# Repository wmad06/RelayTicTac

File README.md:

# RelayTicTac
Relay logic Tic Tac Toe computer
bitfoot is coming!
POTATO!
I like to eat
LEMON!

potato + lemon = sour potato
sour + sweet = 0
sour potato + candy = potato
egg salad
This is a good use of the read me file

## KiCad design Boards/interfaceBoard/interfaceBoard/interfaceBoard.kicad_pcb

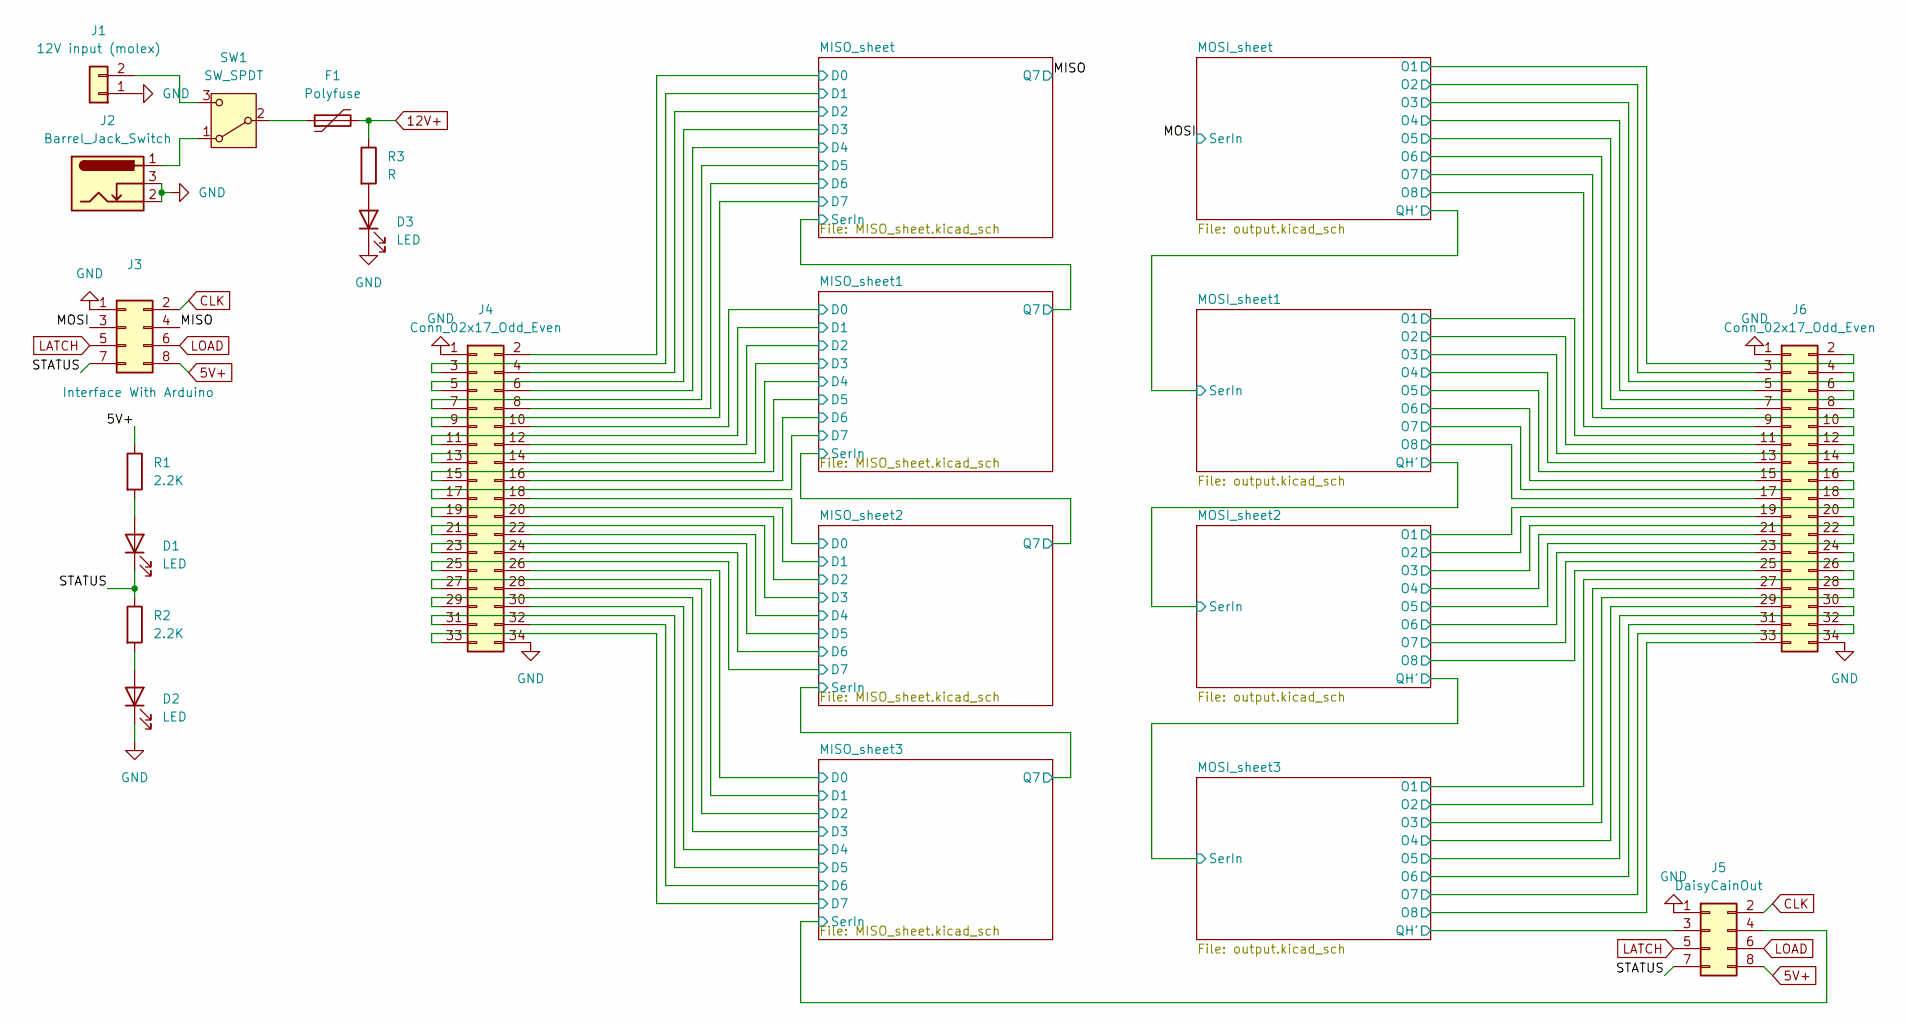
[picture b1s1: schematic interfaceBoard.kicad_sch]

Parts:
D1, D2, D3: LED; LED_D3.0mm
F1: Polyfuse; Fuse_Bourns_MF-RHT100
J1: 12V input (molex); CONN_SD-172648-0000_02_MOL
J2: Barrel_Jack_Switch; BarrelJack_Horizontal
J3: Interface With Arduino; PinHeader_2x04_P2.54mm_Vertical
J4, J6: Conn_02x17_Odd_Even; PinHeader_2x17_P2.54mm_Vertical
J5: DaisyCainOut; PinHeader_2x04_P2.54mm_Vertical
R1, R2: 2.2K; R_Axial_DIN0207_L6.3mm_D2.5mm_P10.16mm_Horizontal
R3: R; R_Axial_DIN0207_L6.3mm_D2.5mm_P10.16mm_Horizontal
SW1: SW_SPDT; SW_SPDT_SS-12D10L5

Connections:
5V+: J3.8, J5.8, R1.1; also elsewhere on the board
12V+: F1.2, R3.1; also elsewhere on the board
/MISO: J3.4; also elsewhere on the board
/MISO_sheet1/D0: J4.10; also elsewhere on the board
/MISO_sheet1/D1: J4.11; also elsewhere on the board
/MISO_sheet1/D2: J4.12; also elsewhere on the board
/MISO_sheet1/D3: J4.13; also elsewhere on the board
/MISO_sheet1/D4: J4.14; also elsewhere on the board
/MISO_sheet1/D5: J4.15; also elsewhere on the board
/MISO_sheet1/D6: J4.16; also elsewhere on the board
/MISO_sheet1/D7: J4.17; also elsewhere on the board
/MISO_sheet2/D0: J4.18; also elsewhere on the board
/MISO_sheet2/D1: J4.19; also elsewhere on the board
/MISO_sheet2/D2: J4.20; also elsewhere on the board
/MISO_sheet2/D3: J4.21; also elsewhere on the board
/MISO_sheet2/D4: J4.22; also elsewhere on the board
/MISO_sheet2/D5: J4.23; also elsewhere on the board
/MISO_sheet2/D6: J4.24; also elsewhere on the board
/MISO_sheet2/D7: J4.25; also elsewhere on the board
/MISO_sheet3/D0: J4.26; also elsewhere on the board
/MISO_sheet3/D1: J4.27; also elsewhere on the board
/MISO_sheet3/D2: J4.28; also elsewhere on the board
/MISO_sheet3/D3: J4.29; also elsewhere on the board
/MISO_sheet3/D4: J4.30; also elsewhere on the board
/MISO_sheet3/D5: J4.31; also elsewhere on the board
/MISO_sheet3/D6: J4.32; also elsewhere on the board
/MISO_sheet3/D7: J4.33; also elsewhere on the board
/MISO_sheet3/SerIn: J5.4; also elsewhere on the board
/MISO_sheet/D0: J4.2; also elsewhere on the board
/MISO_sheet/D1: J4.3; also elsewhere on the board
/MISO_sheet/D2: J4.4; also elsewhere on the board
/MISO_sheet/D3: J4.5; also elsewhere on the board
/MISO_sheet/D4: J4.6; also elsewhere on the board
/MISO_sheet/D5: J4.7; also elsewhere on the board
/MISO_sheet/D6: J4.8; also elsewhere on the board
/MISO_sheet/D7: J4.9; also elsewhere on the board
/MOSI: J3.3; also elsewhere on the board
/MOSI_sheet1/O1: J6.10; also elsewhere on the board
/MOSI_sheet1/O2: J6.11; also elsewhere on the board
/MOSI_sheet1/O3: J6.12; also elsewhere on the board
/MOSI_sheet1/O4: J6.13; also elsewhere on the board
/MOSI_sheet1/O5: J6.14; also elsewhere on the board
/MOSI_sheet1/O6: J6.15; also elsewhere on the board
/MOSI_sheet1/O7: J6.16; also elsewhere on the board
/MOSI_sheet1/O8: J6.17; also elsewhere on the board
/MOSI_sheet2/O1: J6.18; also elsewhere on the board
/MOSI_sheet2/O2: J6.19; also elsewhere on the board
/MOSI_sheet2/O3: J6.20; also elsewhere on the board
/MOSI_sheet2/O4: J6.21; also elsewhere on the board
/MOSI_sheet2/O5: J6.22; also elsewhere on the board
/MOSI_sheet2/O6: J6.23; also elsewhere on the board
/MOSI_sheet2/O7: J6.24; also elsewhere on the board
/MOSI_sheet2/O8: J6.25; also elsewhere on the board
/MOSI_sheet3/O1: J6.26; also elsewhere on the board
/MOSI_sheet3/O2: J6.27; also elsewhere on the board
/MOSI_sheet3/O3: J6.28; also elsewhere on the board
/MOSI_sheet3/O4: J6.29; also elsewhere on the board
/MOSI_sheet3/O5: J6.30; also elsewhere on the board
/MOSI_sheet3/O6: J6.31; also elsewhere on the board
/MOSI_sheet3/O7: J6.32; also elsewhere on the board
/MOSI_sheet3/O8: J6.33; also elsewhere on the board
/MOSI_sheet3/QH': J5.3; also elsewhere on the board
/MOSI_sheet/O1: J6.2; also elsewhere on the board
/MOSI_sheet/O2: J6.3; also elsewhere on the board
/MOSI_sheet/O3: J6.4; also elsewhere on the board
/MOSI_sheet/O4: J6.5; also elsewhere on the board
/MOSI_sheet/O5: J6.6; also elsewhere on the board
/MOSI_sheet/O6: J6.7; also elsewhere on the board
/MOSI_sheet/O7: J6.8; also elsewhere on the board
/MOSI_sheet/O8: J6.9; also elsewhere on the board
/STATUS: D1.1 (K), J3.7, J5.7, R2.1
CLK: J3.2, J5.2; also elsewhere on the board
GND: D2.1 (K), D3.1 (K), J1.1, J2.2, J2.3, J3.1, J4.1, J4.34, J5.1, J6.1, J6.34; also elsewhere on the board
LATCH: J3.5, J5.5; also elsewhere on the board
LOAD: J3.6, J5.6; also elsewhere on the board
unnamed: D1.2 (A), R1.2
unnamed: D2.2 (A), R2.2
unnamed: D3.2 (A), R3.2
unnamed: J1.2, SW1.3 (C)
unnamed: J2.1, SW1.1 (A)
unnamed: F1.1, SW1.2 (B)

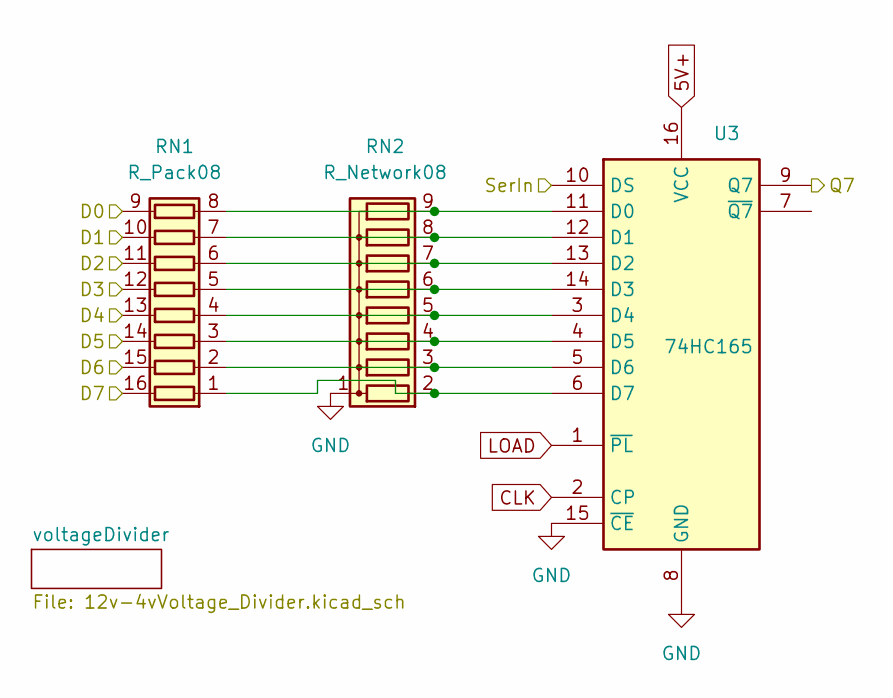
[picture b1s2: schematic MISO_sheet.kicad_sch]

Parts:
RN1: R_Pack08; DIP-16_W7.62mm_Socket
RN2: R_Network08; R_Array_SIP9
U3: 74HC165; DIP-16_W7.62mm_Socket

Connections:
5V+: U3.16 (VCC); also elsewhere on the board
/MISO: U3.9 (Q7); also elsewhere on the board
/MISO_sheet/D0: RN1.9 (R8.2); also elsewhere on the board
/MISO_sheet/D1: RN1.10 (R7.2); also elsewhere on the board
/MISO_sheet/D2: RN1.11 (R6.2); also elsewhere on the board
/MISO_sheet/D3: RN1.12 (R5.2); also elsewhere on the board
/MISO_sheet/D4: RN1.13 (R4.2); also elsewhere on the board
/MISO_sheet/D5: RN1.14 (R3.2); also elsewhere on the board
/MISO_sheet/D6: RN1.15 (R2.2); also elsewhere on the board
/MISO_sheet/D7: RN1.16 (R1.2); also elsewhere on the board
/MISO_sheet/SerIn: U3.10 (DS); also elsewhere on the board
CLK: U3.2 (CP); also elsewhere on the board
GND: RN2.1 (common), U3.8 (GND), U3.15 (~CE); also elsewhere on the board
LOAD: U3.1 (~PL); also elsewhere on the board
unnamed: RN1.1 (R1.1), RN2.2 (R1), U3.6 (D7)
unnamed: RN1.2 (R2.1), RN2.3 (R2), U3.5 (D6)
unnamed: RN1.3 (R3.1), RN2.4 (R3), U3.4 (D5)
unnamed: RN1.4 (R4.1), RN2.5 (R4), U3.3 (D4)
unnamed: RN1.5 (R5.1), RN2.6 (R5), U3.14 (D3)
unnamed: RN1.6 (R6.1), RN2.7 (R6), U3.13 (D2)
unnamed: RN1.7 (R7.1), RN2.8 (R7), U3.12 (D1)
unnamed: RN1.8 (R8.1), RN2.9 (R8), U3.11 (D0)

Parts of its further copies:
RN3, RN5, RN7: R_Pack08; DIP-16_W7.62mm_Socket
RN4, RN6, RN8: R_Network08; R_Array_SIP9
U6, U9, U12: 74HC165; DIP-16_W7.62mm_Socket

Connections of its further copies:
5V+: U6.16 (VCC), U9.16 (VCC), U12.16 (VCC); also elsewhere on the board
/MISO_sheet1/D0: RN3.9 (R8.2); also elsewhere on the board
/MISO_sheet1/D1: RN3.10 (R7.2); also elsewhere on the board
/MISO_sheet1/D2: RN3.11 (R6.2); also elsewhere on the board
/MISO_sheet1/D3: RN3.12 (R5.2); also elsewhere on the board
/MISO_sheet1/D4: RN3.13 (R4.2); also elsewhere on the board
/MISO_sheet1/D5: RN3.14 (R3.2); also elsewhere on the board
/MISO_sheet1/D6: RN3.15 (R2.2); also elsewhere on the board
/MISO_sheet1/D7: RN3.16 (R1.2); also elsewhere on the board
/MISO_sheet1/SerIn: U6.10 (DS), U9.9 (Q7)
/MISO_sheet2/D0: RN5.9 (R8.2); also elsewhere on the board
/MISO_sheet2/D1: RN5.10 (R7.2); also elsewhere on the board
/MISO_sheet2/D2: RN5.11 (R6.2); also elsewhere on the board
/MISO_sheet2/D3: RN5.12 (R5.2); also elsewhere on the board
/MISO_sheet2/D4: RN5.13 (R4.2); also elsewhere on the board
/MISO_sheet2/D5: RN5.14 (R3.2); also elsewhere on the board
/MISO_sheet2/D6: RN5.15 (R2.2); also elsewhere on the board
/MISO_sheet2/D7: RN5.16 (R1.2); also elsewhere on the board
/MISO_sheet2/SerIn: U9.10 (DS), U12.9 (Q7)
/MISO_sheet3/D0: RN7.9 (R8.2); also elsewhere on the board
/MISO_sheet3/D1: RN7.10 (R7.2); also elsewhere on the board
/MISO_sheet3/D2: RN7.11 (R6.2); also elsewhere on the board
/MISO_sheet3/D3: RN7.12 (R5.2); also elsewhere on the board
/MISO_sheet3/D4: RN7.13 (R4.2); also elsewhere on the board
/MISO_sheet3/D5: RN7.14 (R3.2); also elsewhere on the board
/MISO_sheet3/D6: RN7.15 (R2.2); also elsewhere on the board
/MISO_sheet3/D7: RN7.16 (R1.2); also elsewhere on the board
/MISO_sheet3/SerIn: U12.10 (DS); also elsewhere on the board
/MISO_sheet/SerIn: U6.9 (Q7); also elsewhere on the board
CLK: U6.2 (CP), U9.2 (CP), U12.2 (CP); also elsewhere on the board
GND: RN4.1 (common), RN6.1 (common), RN8.1 (common), U6.8 (GND), U6.15 (~CE), U9.8 (GND), U9.15 (~CE), U12.8 (GND), U12.15 (~CE); also elsewhere on the board
LOAD: U6.1 (~PL), U9.1 (~PL), U12.1 (~PL); also elsewhere on the board
unnamed: RN3.1 (R1.1), RN4.2 (R1), U6.6 (D7)
unnamed: RN3.2 (R2.1), RN4.3 (R2), U6.5 (D6)
unnamed: RN3.3 (R3.1), RN4.4 (R3), U6.4 (D5)
unnamed: RN3.4 (R4.1), RN4.5 (R4), U6.3 (D4)
unnamed: RN3.5 (R5.1), RN4.6 (R5), U6.14 (D3)
unnamed: RN3.6 (R6.1), RN4.7 (R6), U6.13 (D2)
unnamed: RN3.7 (R7.1), RN4.8 (R7), U6.12 (D1)
unnamed: RN3.8 (R8.1), RN4.9 (R8), U6.11 (D0)
unnamed: RN5.1 (R1.1), RN6.2 (R1), U9.6 (D7)
unnamed: RN5.2 (R2.1), RN6.3 (R2), U9.5 (D6)
unnamed: RN5.3 (R3.1), RN6.4 (R3), U9.4 (D5)
unnamed: RN5.4 (R4.1), RN6.5 (R4), U9.3 (D4)
unnamed: RN5.5 (R5.1), RN6.6 (R5), U9.14 (D3)
unnamed: RN5.6 (R6.1), RN6.7 (R6), U9.13 (D2)
unnamed: RN5.7 (R7.1), RN6.8 (R7), U9.12 (D1)
unnamed: RN5.8 (R8.1), RN6.9 (R8), U9.11 (D0)
unnamed: RN7.1 (R1.1), RN8.2 (R1), U12.6 (D7)
unnamed: RN7.2 (R2.1), RN8.3 (R2), U12.5 (D6)
unnamed: RN7.3 (R3.1), RN8.4 (R3), U12.4 (D5)
unnamed: RN7.4 (R4.1), RN8.5 (R4), U12.3 (D4)
unnamed: RN7.5 (R5.1), RN8.6 (R5), U12.14 (D3)
unnamed: RN7.6 (R6.1), RN8.7 (R6), U12.13 (D2)
unnamed: RN7.7 (R7.1), RN8.8 (R7), U12.12 (D1)
unnamed: RN7.8 (R8.1), RN8.9 (R8), U12.11 (D0)

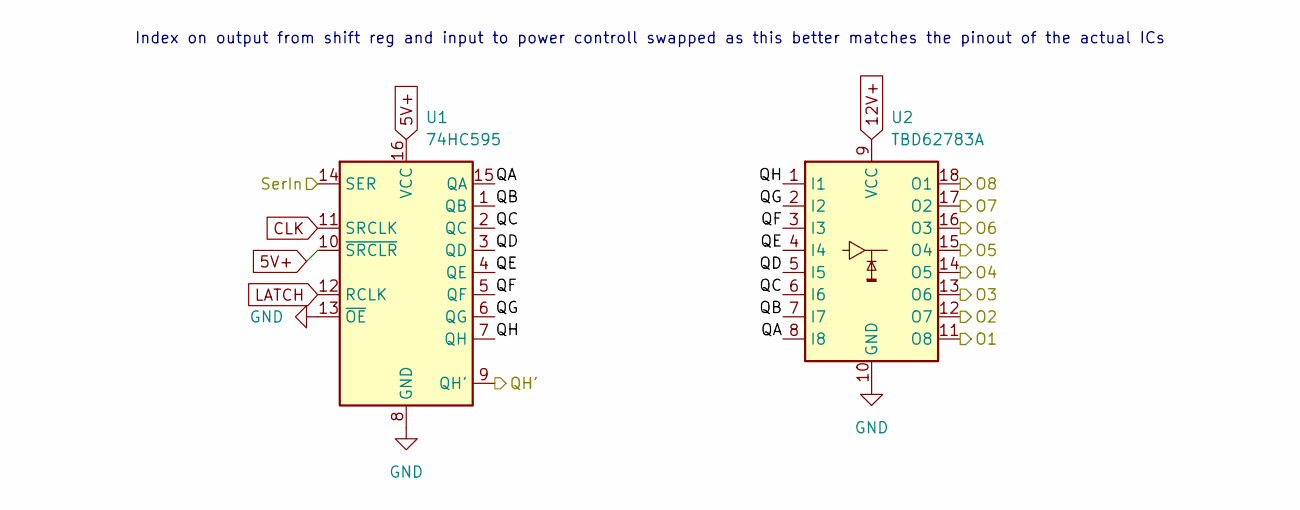
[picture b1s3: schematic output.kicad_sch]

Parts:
U1: 74HC595; DIP-16_W7.62mm_Socket
U2: TBD62783A; DIP-18_W7.62mm_Socket

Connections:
5V+: U1.10 (~SRCLR), U1.16 (VCC); also elsewhere on the board
12V+: U2.9 (VCC); also elsewhere on the board
/MOSI: U1.14 (SER); also elsewhere on the board
/MOSI_sheet/O1: U2.11 (O8); also elsewhere on the board
/MOSI_sheet/O2: U2.12 (O7); also elsewhere on the board
/MOSI_sheet/O3: U2.13 (O6); also elsewhere on the board
/MOSI_sheet/O4: U2.14 (O5); also elsewhere on the board
/MOSI_sheet/O5: U2.15 (O4); also elsewhere on the board
/MOSI_sheet/O6: U2.16 (O3); also elsewhere on the board
/MOSI_sheet/O7: U2.17 (O2); also elsewhere on the board
/MOSI_sheet/O8: U2.18 (O1); also elsewhere on the board
/MOSI_sheet/QA: U1.15 (QA), U2.8 (I8)
/MOSI_sheet/QB: U1.1 (QB), U2.7 (I7)
/MOSI_sheet/QC: U1.2 (QC), U2.6 (I6)
/MOSI_sheet/QD: U1.3 (QD), U2.5 (I5)
/MOSI_sheet/QE: U1.4 (QE), U2.4 (I4)
/MOSI_sheet/QF: U1.5 (QF), U2.3 (I3)
/MOSI_sheet/QG: U1.6 (QG), U2.2 (I2)
/MOSI_sheet/QH: U1.7 (QH), U2.1 (I1)
/MOSI_sheet/QH': U1.9 (QH'); also elsewhere on the board
CLK: U1.11 (SRCLK); also elsewhere on the board
GND: U1.8 (GND), U1.13 (~OE), U2.10 (GND); also elsewhere on the board
LATCH: U1.12 (RCLK); also elsewhere on the board

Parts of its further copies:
U4, U7, U10: 74HC595; DIP-16_W7.62mm_Socket
U5, U8, U11: TBD62783A; DIP-18_W7.62mm_Socket

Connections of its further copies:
5V+: U4.10 (~SRCLR), U4.16 (VCC), U7.10 (~SRCLR), U7.16 (VCC), U10.10 (~SRCLR), U10.16 (VCC); also elsewhere on the board
12V+: U5.9 (VCC), U8.9 (VCC), U11.9 (VCC); also elsewhere on the board
/MOSI_sheet1/O1: U5.11 (O8); also elsewhere on the board
/MOSI_sheet1/O2: U5.12 (O7); also elsewhere on the board
/MOSI_sheet1/O3: U5.13 (O6); also elsewhere on the board
/MOSI_sheet1/O4: U5.14 (O5); also elsewhere on the board
/MOSI_sheet1/O5: U5.15 (O4); also elsewhere on the board
/MOSI_sheet1/O6: U5.16 (O3); also elsewhere on the board
/MOSI_sheet1/O7: U5.17 (O2); also elsewhere on the board
/MOSI_sheet1/O8: U5.18 (O1); also elsewhere on the board
/MOSI_sheet1/QA: U4.15 (QA), U5.8 (I8)
/MOSI_sheet1/QB: U4.1 (QB), U5.7 (I7)
/MOSI_sheet1/QC: U4.2 (QC), U5.6 (I6)
/MOSI_sheet1/QD: U4.3 (QD), U5.5 (I5)
/MOSI_sheet1/QE: U4.4 (QE), U5.4 (I4)
/MOSI_sheet1/QF: U4.5 (QF), U5.3 (I3)
/MOSI_sheet1/QG: U4.6 (QG), U5.2 (I2)
/MOSI_sheet1/QH: U4.7 (QH), U5.1 (I1)
/MOSI_sheet1/QH': U4.9 (QH'), U7.14 (SER)
/MOSI_sheet2/O1: U8.11 (O8); also elsewhere on the board
/MOSI_sheet2/O2: U8.12 (O7); also elsewhere on the board
/MOSI_sheet2/O3: U8.13 (O6); also elsewhere on the board
/MOSI_sheet2/O4: U8.14 (O5); also elsewhere on the board
/MOSI_sheet2/O5: U8.15 (O4); also elsewhere on the board
/MOSI_sheet2/O6: U8.16 (O3); also elsewhere on the board
/MOSI_sheet2/O7: U8.17 (O2); also elsewhere on the board
/MOSI_sheet2/O8: U8.18 (O1); also elsewhere on the board
/MOSI_sheet2/QA: U7.15 (QA), U8.8 (I8)
/MOSI_sheet2/QB: U7.1 (QB), U8.7 (I7)
/MOSI_sheet2/QC: U7.2 (QC), U8.6 (I6)
/MOSI_sheet2/QD: U7.3 (QD), U8.5 (I5)
/MOSI_sheet2/QE: U7.4 (QE), U8.4 (I4)
/MOSI_sheet2/QF: U7.5 (QF), U8.3 (I3)
/MOSI_sheet2/QG: U7.6 (QG), U8.2 (I2)
/MOSI_sheet2/QH: U7.7 (QH), U8.1 (I1)
/MOSI_sheet2/QH': U7.9 (QH'), U10.14 (SER)
/MOSI_sheet3/O1: U11.11 (O8); also elsewhere on the board
/MOSI_sheet3/O2: U11.12 (O7); also elsewhere on the board
/MOSI_sheet3/O3: U11.13 (O6); also elsewhere on the board
/MOSI_sheet3/O4: U11.14 (O5); also elsewhere on the board
/MOSI_sheet3/O5: U11.15 (O4); also elsewhere on the board
/MOSI_sheet3/O6: U11.16 (O3); also elsewhere on the board
/MOSI_sheet3/O7: U11.17 (O2); also elsewhere on the board
/MOSI_sheet3/O8: U11.18 (O1); also elsewhere on the board
/MOSI_sheet3/QA: U10.15 (QA), U11.8 (I8)
/MOSI_sheet3/QB: U10.1 (QB), U11.7 (I7)
/MOSI_sheet3/QC: U10.2 (QC), U11.6 (I6)
/MOSI_sheet3/QD: U10.3 (QD), U11.5 (I5)
/MOSI_sheet3/QE: U10.4 (QE), U11.4 (I4)
/MOSI_sheet3/QF: U10.5 (QF), U11.3 (I3)
/MOSI_sheet3/QG: U10.6 (QG), U11.2 (I2)
/MOSI_sheet3/QH: U10.7 (QH), U11.1 (I1)
/MOSI_sheet3/QH': U10.9 (QH'); also elsewhere on the board
/MOSI_sheet/QH': U4.14 (SER); also elsewhere on the board
CLK: U4.11 (SRCLK), U7.11 (SRCLK), U10.11 (SRCLK); also elsewhere on the board
GND: U4.8 (GND), U4.13 (~OE), U5.10 (GND), U7.8 (GND), U7.13 (~OE), U8.10 (GND), U10.8 (GND), U10.13 (~OE), U11.10 (GND); also elsewhere on the board
LATCH: U4.12 (RCLK), U7.12 (RCLK), U10.12 (RCLK); also elsewhere on the board

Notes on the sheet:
Index on output from shift reg and input to power controll swapped as this better matches the pinout of the actual ICs

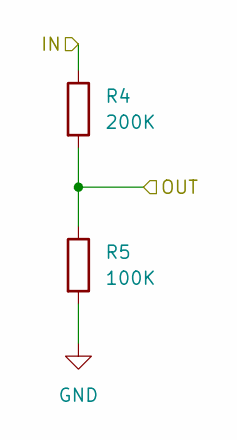
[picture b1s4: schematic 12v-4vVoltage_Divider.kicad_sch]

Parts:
R4: 200K; R_Axial_DIN0207_L6.3mm_D2.5mm_P10.16mm_Horizontal
R5: 100K; R_Axial_DIN0207_L6.3mm_D2.5mm_P10.16mm_Horizontal

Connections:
unnamed: R4.2, R5.1

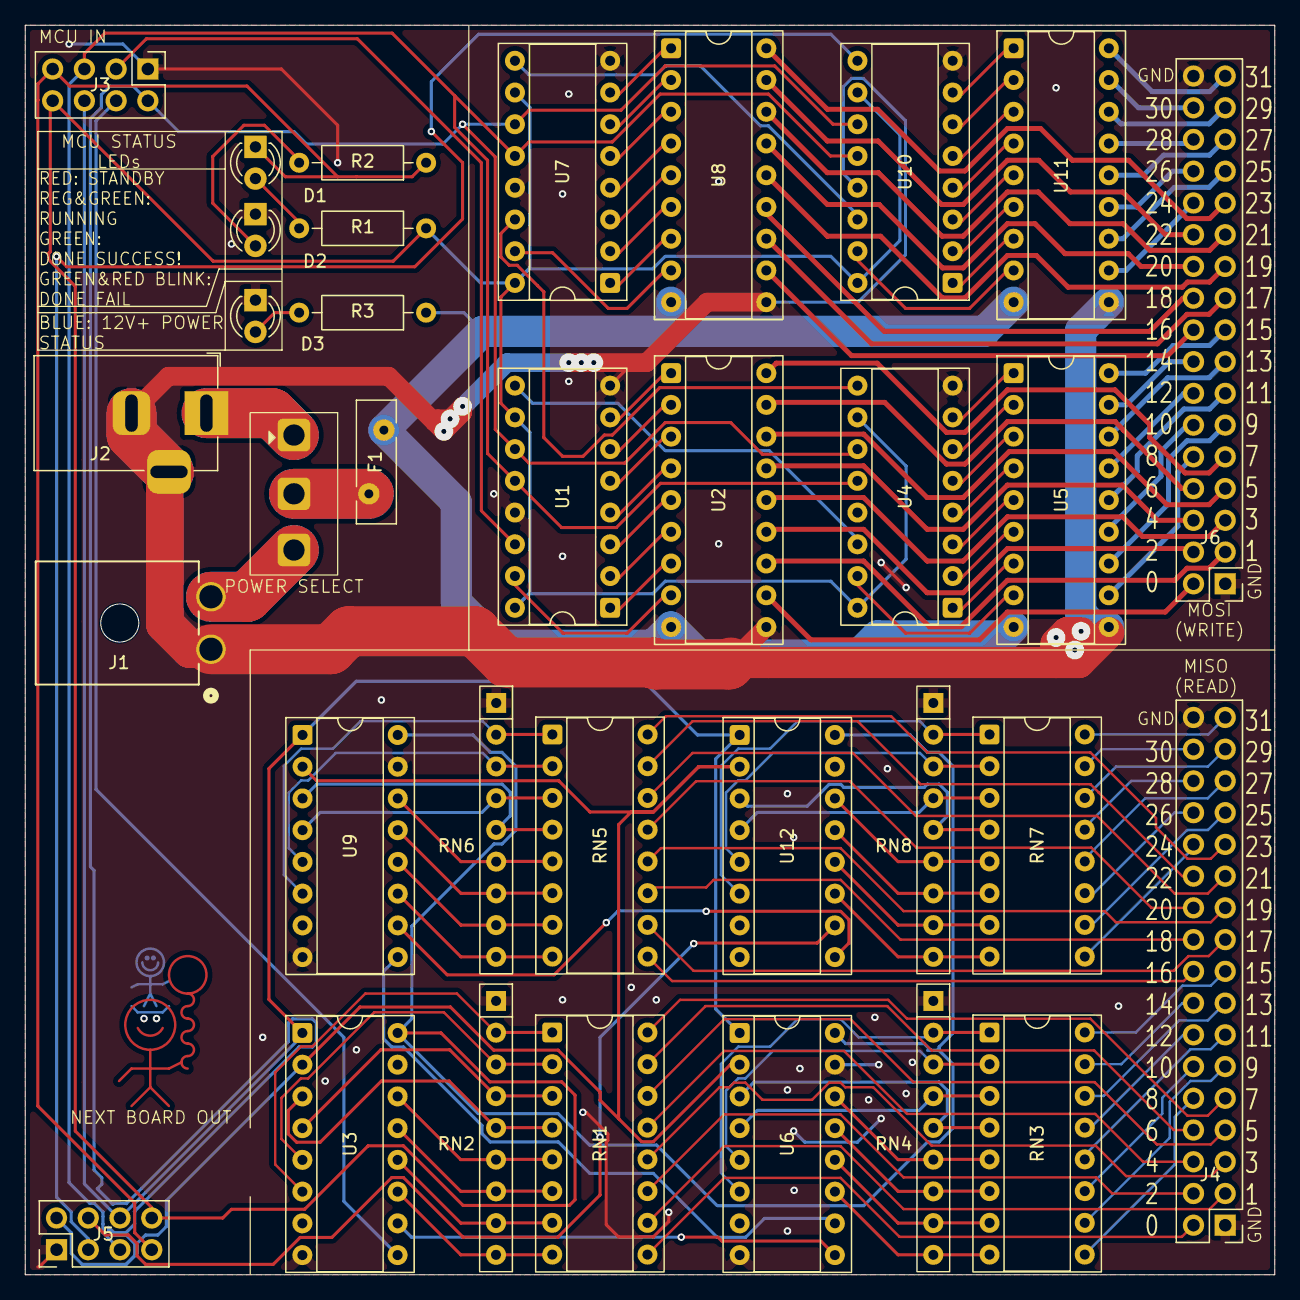
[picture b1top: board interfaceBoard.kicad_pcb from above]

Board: 2 copper layers, 100.0 x 100.0 mm, 34 parts (0 on the bottom side), 151 nets.

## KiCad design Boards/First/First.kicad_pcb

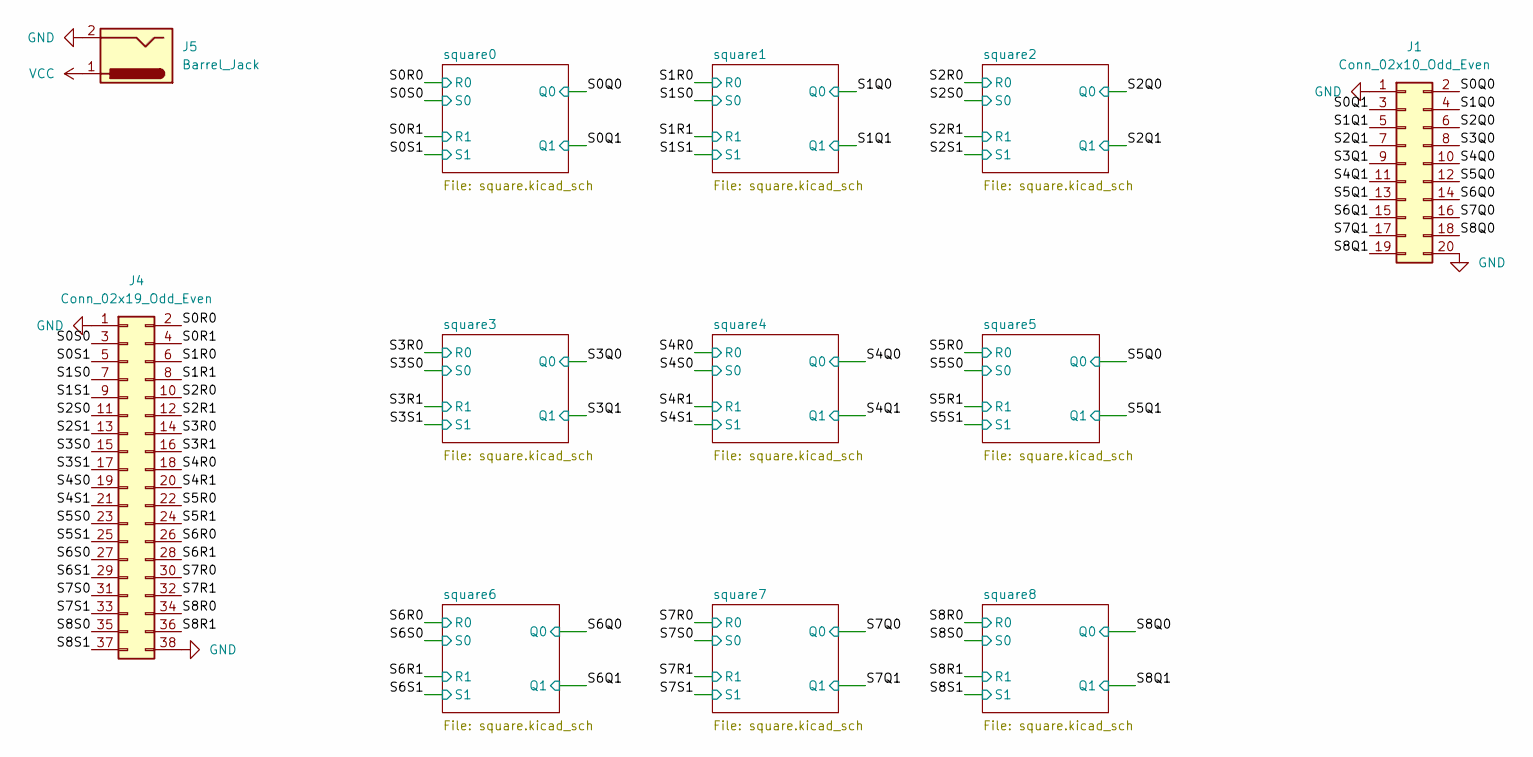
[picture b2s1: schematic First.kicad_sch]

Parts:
J1: Conn_02x10_Odd_Even; IDC-Header_2x10_P2.54mm_Latch_Vertical
J4: Conn_02x19_Odd_Even; PinHeader_2x19_P2.54mm_Vertical
J5: Barrel_Jack; BarrelJack_Horizontal

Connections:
/S0Q0: J1.2; also elsewhere on the board
/S0Q1: J1.3; also elsewhere on the board
/S0R0: J4.2; also elsewhere on the board
/S0R1: J4.4; also elsewhere on the board
/S0S0: J4.3; also elsewhere on the board
/S0S1: J4.5; also elsewhere on the board
/S1Q0: J1.4; also elsewhere on the board
/S1Q1: J1.5; also elsewhere on the board
/S1R0: J4.6; also elsewhere on the board
/S1R1: J4.8; also elsewhere on the board
/S1S0: J4.7; also elsewhere on the board
/S1S1: J4.9; also elsewhere on the board
/S2Q0: J1.6; also elsewhere on the board
/S2Q1: J1.7; also elsewhere on the board
/S2R0: J4.10; also elsewhere on the board
/S2R1: J4.12; also elsewhere on the board
/S2S0: J4.11; also elsewhere on the board
/S2S1: J4.13; also elsewhere on the board
/S3Q0: J1.8; also elsewhere on the board
/S3Q1: J1.9; also elsewhere on the board
/S3R0: J4.14; also elsewhere on the board
/S3R1: J4.16; also elsewhere on the board
/S3S0: J4.15; also elsewhere on the board
/S3S1: J4.17; also elsewhere on the board
/S4Q0: J1.10; also elsewhere on the board
/S4Q1: J1.11; also elsewhere on the board
/S4R0: J4.18; also elsewhere on the board
/S4R1: J4.20; also elsewhere on the board
/S4S0: J4.19; also elsewhere on the board
/S4S1: J4.21; also elsewhere on the board
/S5Q0: J1.12; also elsewhere on the board
/S5Q1: J1.13; also elsewhere on the board
/S5R0: J4.22; also elsewhere on the board
/S5R1: J4.24; also elsewhere on the board
/S5S0: J4.23; also elsewhere on the board
/S5S1: J4.25; also elsewhere on the board
/S6Q0: J1.14; also elsewhere on the board
/S6Q1: J1.15; also elsewhere on the board
/S6R0: J4.26; also elsewhere on the board
/S6R1: J4.28; also elsewhere on the board
/S6S0: J4.27; also elsewhere on the board
/S6S1: J4.29; also elsewhere on the board
/S7Q0: J1.16; also elsewhere on the board
/S7Q1: J1.17; also elsewhere on the board
/S7R0: J4.30; also elsewhere on the board
/S7R1: J4.32; also elsewhere on the board
/S7S0: J4.31; also elsewhere on the board
/S7S1: J4.33; also elsewhere on the board
/S8Q0: J1.18; also elsewhere on the board
/S8Q1: J1.19; also elsewhere on the board
/S8R0: J4.34; also elsewhere on the board
/S8R1: J4.36; also elsewhere on the board
/S8S0: J4.35; also elsewhere on the board
/S8S1: J4.37; also elsewhere on the board
GND: J1.1, J1.20, J4.1, J4.38, J5.2; also elsewhere on the board
VCC: J5.1; also elsewhere on the board

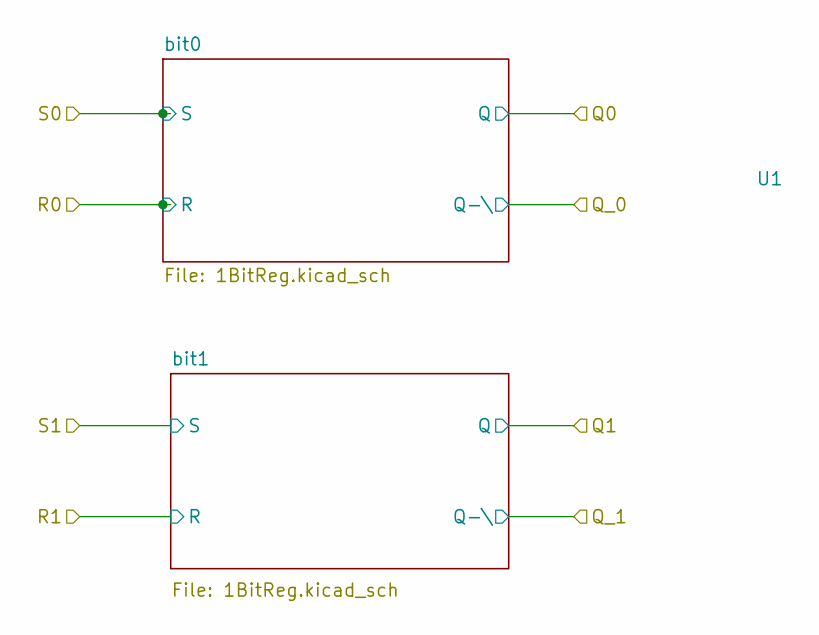
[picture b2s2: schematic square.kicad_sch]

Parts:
U1: squareRegOutSilk

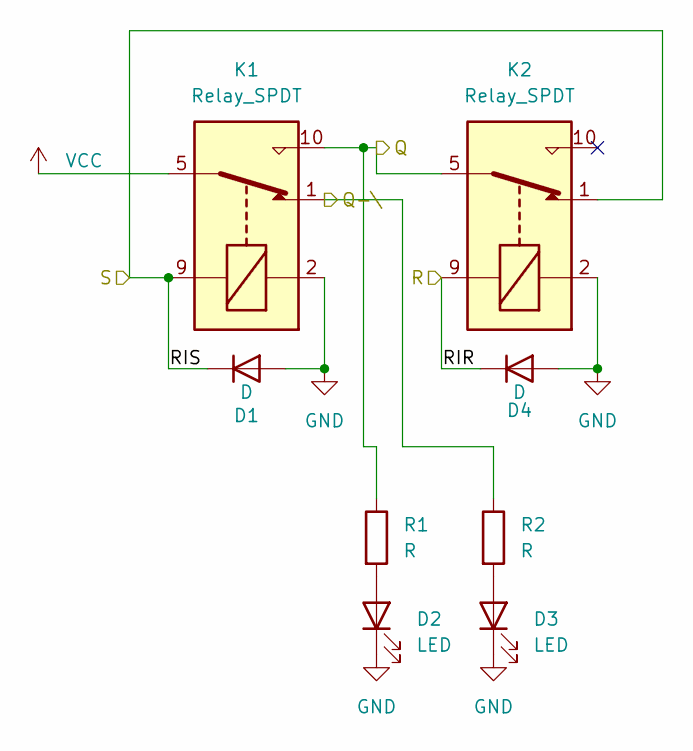
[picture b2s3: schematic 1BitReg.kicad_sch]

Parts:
D1, D4: D; D_DO-35_SOD27_P7.62mm_Horizontal
D2, D3: LED; LED_D3.0mm
K1, K2: Relay_SPDT; Relay_SPDT_Omron_G5V-1
R1, R2: R; R_Axial_DIN0207_L6.3mm_D2.5mm_P7.62mm_Horizontal

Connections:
/S0Q0: K1.10, K2.5, K2.6, R1.1; also elsewhere on the board
/S0R0: D4.1 (K), K2.9; also elsewhere on the board
/S0S0: D1.1 (K), K1.9, K2.1; also elsewhere on the board
/square0/Q_0: K1.1, R2.1
GND: D1.2 (A), D2.1 (K), D3.1 (K), D4.2 (A), K1.2, K2.2; also elsewhere on the board
unnamed: D2.2 (A), R1.2
unnamed: D3.2 (A), R2.2
VCC: K1.5, K1.6; also elsewhere on the board

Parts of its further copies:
D5, D8, D9, D12, D13, D16, D17, D20, D21, D24, D25, D28, D29, D32, D33, D36, D37, D40, D41, D44, D45, D48, D49, D52, D53, D56, D57, D60, D61, D64, D65, D68, D69, D72: D; D_DO-35_SOD27_P7.62mm_Horizontal
D6, D7, D10, D11, D14, D15, D18, D19, D22, D23, D26, D27, D30, D31, D34, D35, D38, D39, D42, D43, D46, D47, D50, D51, D54, D55, D58, D59, D62, D63, D66, D67, D70, D71: LED; LED_D3.0mm
K3, K4, K5, K6, K7, K8, K9, K10, K11, K12, K13, K14, K15, K16, K17, K18, K19, K20, K21, K22, K23, K24, K25, K26, K27, K28, K29, K30, K31, K32, K33, K34, K35, K36: Relay_SPDT; Relay_SPDT_Omron_G5V-1
R3, R4, R5, R6, R7, R8, R9, R10, R11, R12, R13, R14, R15, R16, R17, R18, R19, R20, R21, R22, R23, R24, R25, R26, R27, R28, R29, R30, R31, R32, R33, R34, R35, R36: R; R_Axial_DIN0207_L6.3mm_D2.5mm_P7.62mm_Horizontal

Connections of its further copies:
/S0Q1: K3.10, K4.5, K4.6, R3.1; also elsewhere on the board
/S0R1: D8.1 (K), K4.9; also elsewhere on the board
/S0S1: D5.1 (K), K3.9, K4.1; also elsewhere on the board
/S1Q0: K5.10, K6.5, K6.6, R5.1; also elsewhere on the board
/S1Q1: K7.10, K8.5, K8.6, R7.1; also elsewhere on the board
/S1R0: D12.1 (K), K6.9; also elsewhere on the board
/S1R1: D16.1 (K), K8.9; also elsewhere on the board
/S1S0: D9.1 (K), K5.9, K6.1; also elsewhere on the board
/S1S1: D13.1 (K), K7.9, K8.1; also elsewhere on the board
/S2Q0: K9.10, K10.5, K10.6, R9.1; also elsewhere on the board
/S2Q1: K11.10, K12.5, K12.6, R11.1; also elsewhere on the board
/S2R0: D20.1 (K), K10.9; also elsewhere on the board
/S2R1: D24.1 (K), K12.9; also elsewhere on the board
/S2S0: D17.1 (K), K9.9, K10.1; also elsewhere on the board
/S2S1: D21.1 (K), K11.9, K12.1; also elsewhere on the board
/S3Q0: K13.10, K14.5, K14.6, R13.1; also elsewhere on the board
/S3Q1: K15.10, K16.5, K16.6, R15.1; also elsewhere on the board
/S3R0: D28.1 (K), K14.9; also elsewhere on the board
/S3R1: D32.1 (K), K16.9; also elsewhere on the board
/S3S0: D25.1 (K), K13.9, K14.1; also elsewhere on the board
/S3S1: D29.1 (K), K15.9, K16.1; also elsewhere on the board
/S4Q0: K17.10, K18.5, K18.6, R17.1; also elsewhere on the board
/S4Q1: K19.10, K20.5, K20.6, R19.1; also elsewhere on the board
/S4R0: D36.1 (K), K18.9; also elsewhere on the board
/S4R1: D40.1 (K), K20.9; also elsewhere on the board
/S4S0: D33.1 (K), K17.9, K18.1; also elsewhere on the board
/S4S1: D37.1 (K), K19.9, K20.1; also elsewhere on the board
/S5Q0: K21.10, K22.5, K22.6, R21.1; also elsewhere on the board
/S5Q1: K23.10, K24.5, K24.6, R23.1; also elsewhere on the board
/S5R0: D44.1 (K), K22.9; also elsewhere on the board
/S5R1: D48.1 (K), K24.9; also elsewhere on the board
/S5S0: D41.1 (K), K21.9, K22.1; also elsewhere on the board
/S5S1: D45.1 (K), K23.9, K24.1; also elsewhere on the board
/S6Q0: K25.10, K26.5, K26.6, R25.1; also elsewhere on the board
/S6Q1: K27.10, K28.5, K28.6, R27.1; also elsewhere on the board
/S6R0: D52.1 (K), K26.9; also elsewhere on the board
/S6R1: D56.1 (K), K28.9; also elsewhere on the board
/S6S0: D49.1 (K), K25.9, K26.1; also elsewhere on the board
/S6S1: D53.1 (K), K27.9, K28.1; also elsewhere on the board
/S7Q0: K29.10, K30.5, K30.6, R29.1; also elsewhere on the board
/S7Q1: K31.10, K32.5, K32.6, R31.1; also elsewhere on the board
/S7R0: D60.1 (K), K30.9; also elsewhere on the board
/S7R1: D64.1 (K), K32.9; also elsewhere on the board
/S7S0: D57.1 (K), K29.9, K30.1; also elsewhere on the board
/S7S1: D61.1 (K), K31.9, K32.1; also elsewhere on the board
/S8Q0: K33.10, K34.5, K34.6, R33.1; also elsewhere on the board
/S8Q1: K35.10, K36.5, K36.6, R35.1; also elsewhere on the board
/S8R0: D68.1 (K), K34.9; also elsewhere on the board
/S8R1: D72.1 (K), K36.9; also elsewhere on the board
/S8S0: D65.1 (K), K33.9, K34.1; also elsewhere on the board
/S8S1: D69.1 (K), K35.9, K36.1; also elsewhere on the board
/square0/Q_1: K3.1, R4.1
/square1/Q_0: K5.1, R6.1
/square1/Q_1: K7.1, R8.1
/square2/Q_0: K9.1, R10.1
/square2/Q_1: K11.1, R12.1
/square3/Q_0: K13.1, R14.1
/square3/Q_1: K15.1, R16.1
/square4/Q_0: K17.1, R18.1
/square4/Q_1: K19.1, R20.1
/square5/Q_0: K21.1, R22.1
/square5/Q_1: K23.1, R24.1
/square6/Q_0: K25.1, R26.1
/square6/Q_1: K27.1, R28.1
/square7/Q_0: K29.1, R30.1
/square7/Q_1: K31.1, R32.1
/square8/Q_0: K33.1, R34.1
/square8/Q_1: K35.1, R36.1
GND: D5.2 (A), D6.1 (K), D7.1 (K), D8.2 (A), D9.2 (A), D10.1 (K), D11.1 (K), D12.2 (A), D13.2 (A), D14.1 (K), D15.1 (K), D16.2 (A), D17.2 (A), D18.1 (K), D19.1 (K), D20.2 (A), D21.2 (A), D22.1 (K), D23.1 (K), D24.2 (A), D25.2 (A), D26.1 (K), D27.1 (K), D28.2 (A), D29.2 (A), D30.1 (K), D31.1 (K), D32.2 (A), D33.2 (A), D34.1 (K), D35.1 (K), D36.2 (A), D37.2 (A), D38.1 (K), D39.1 (K), D40.2 (A), D41.2 (A), D42.1 (K), D43.1 (K), D44.2 (A), D45.2 (A), D46.1 (K), D47.1 (K), D48.2 (A), D49.2 (A), D50.1 (K), D51.1 (K), D52.2 (A), D53.2 (A), D54.1 (K), D55.1 (K), D56.2 (A), D57.2 (A), D58.1 (K), D59.1 (K), D60.2 (A), D61.2 (A), D62.1 (K), D63.1 (K), D64.2 (A), D65.2 (A), D66.1 (K), D67.1 (K), D68.2 (A), D69.2 (A), D70.1 (K), D71.1 (K), D72.2 (A), K3.2, K4.2, K5.2, K6.2, K7.2, K8.2, K9.2, K10.2, K11.2, K12.2, K13.2, K14.2, K15.2, K16.2, K17.2, K18.2, K19.2, K20.2, K21.2, K22.2, K23.2, K24.2, K25.2, K26.2, K27.2, K28.2, K29.2, K30.2, K31.2, K32.2, K33.2, K34.2, K35.2, K36.2; also elsewhere on the board
unnamed: D6.2 (A), R3.2
unnamed: D7.2 (A), R4.2
unnamed: D10.2 (A), R5.2
unnamed: D11.2 (A), R6.2
unnamed: D14.2 (A), R7.2
unnamed: D15.2 (A), R8.2
unnamed: D18.2 (A), R9.2
unnamed: D19.2 (A), R10.2
unnamed: D22.2 (A), R11.2
unnamed: D23.2 (A), R12.2
unnamed: D26.2 (A), R13.2
unnamed: D27.2 (A), R14.2
unnamed: D30.2 (A), R15.2
unnamed: D31.2 (A), R16.2
unnamed: D34.2 (A), R17.2
unnamed: D35.2 (A), R18.2
unnamed: D38.2 (A), R19.2
unnamed: D39.2 (A), R20.2
unnamed: D42.2 (A), R21.2
unnamed: D43.2 (A), R22.2
unnamed: D46.2 (A), R23.2
unnamed: D47.2 (A), R24.2
unnamed: D50.2 (A), R25.2
unnamed: D51.2 (A), R26.2
unnamed: D54.2 (A), R27.2
unnamed: D55.2 (A), R28.2
unnamed: D58.2 (A), R29.2
unnamed: D59.2 (A), R30.2
unnamed: D62.2 (A), R31.2
unnamed: D63.2 (A), R32.2
unnamed: D66.2 (A), R33.2
unnamed: D67.2 (A), R34.2
unnamed: D70.2 (A), R35.2
unnamed: D71.2 (A), R36.2
VCC: K3.5, K3.6, K5.5, K5.6, K7.5, K7.6, K9.5, K9.6, K11.5, K11.6, K13.5, K13.6, K15.5, K15.6, K17.5, K17.6, K19.5, K19.6, K21.5, K21.6, K23.5, K23.6, K25.5, K25.6, K27.5, K27.6, K29.5, K29.6, K31.5, K31.6, K33.5, K33.6, K35.5, K35.6; also elsewhere on the board
